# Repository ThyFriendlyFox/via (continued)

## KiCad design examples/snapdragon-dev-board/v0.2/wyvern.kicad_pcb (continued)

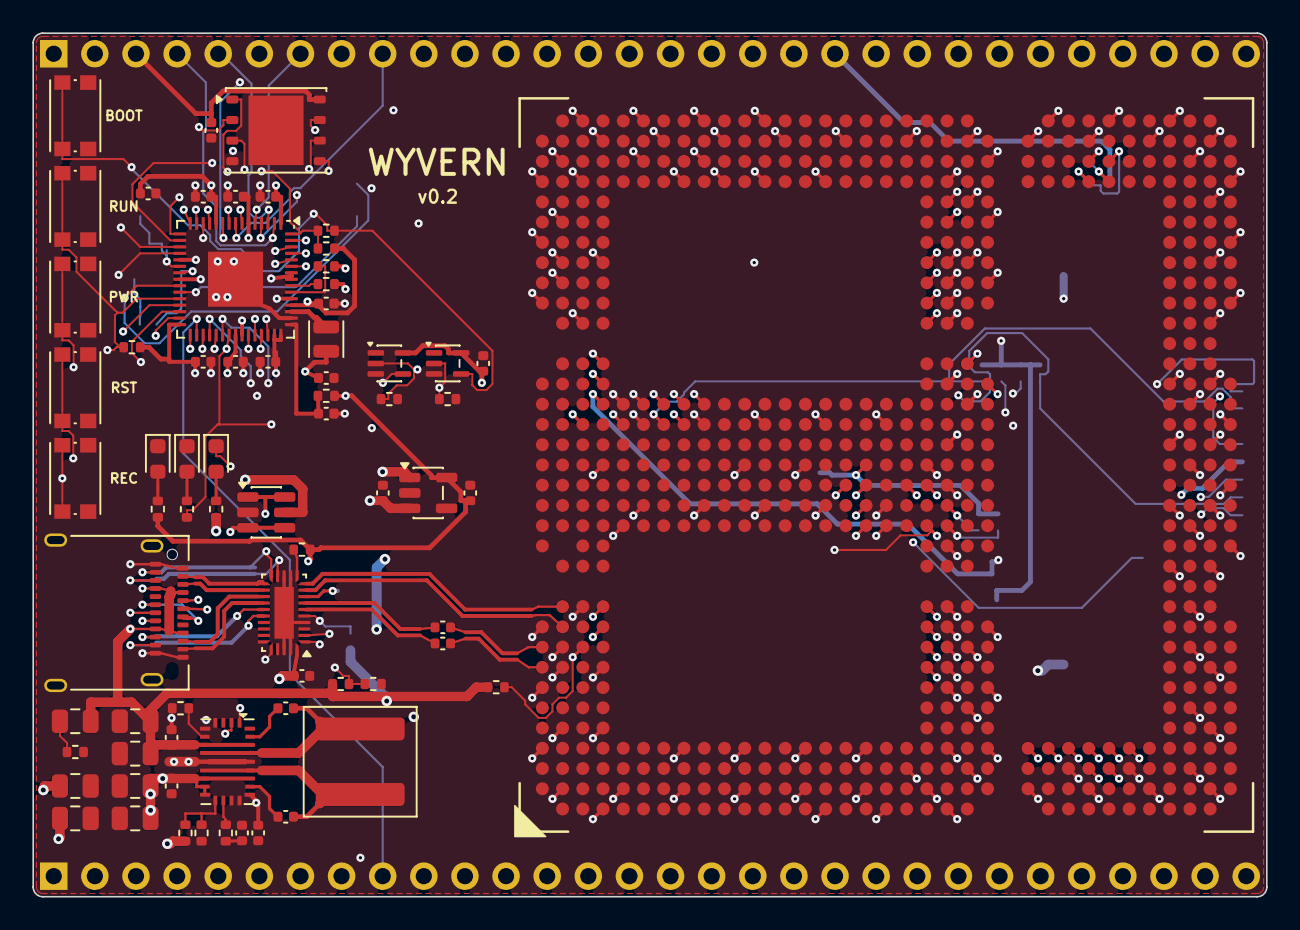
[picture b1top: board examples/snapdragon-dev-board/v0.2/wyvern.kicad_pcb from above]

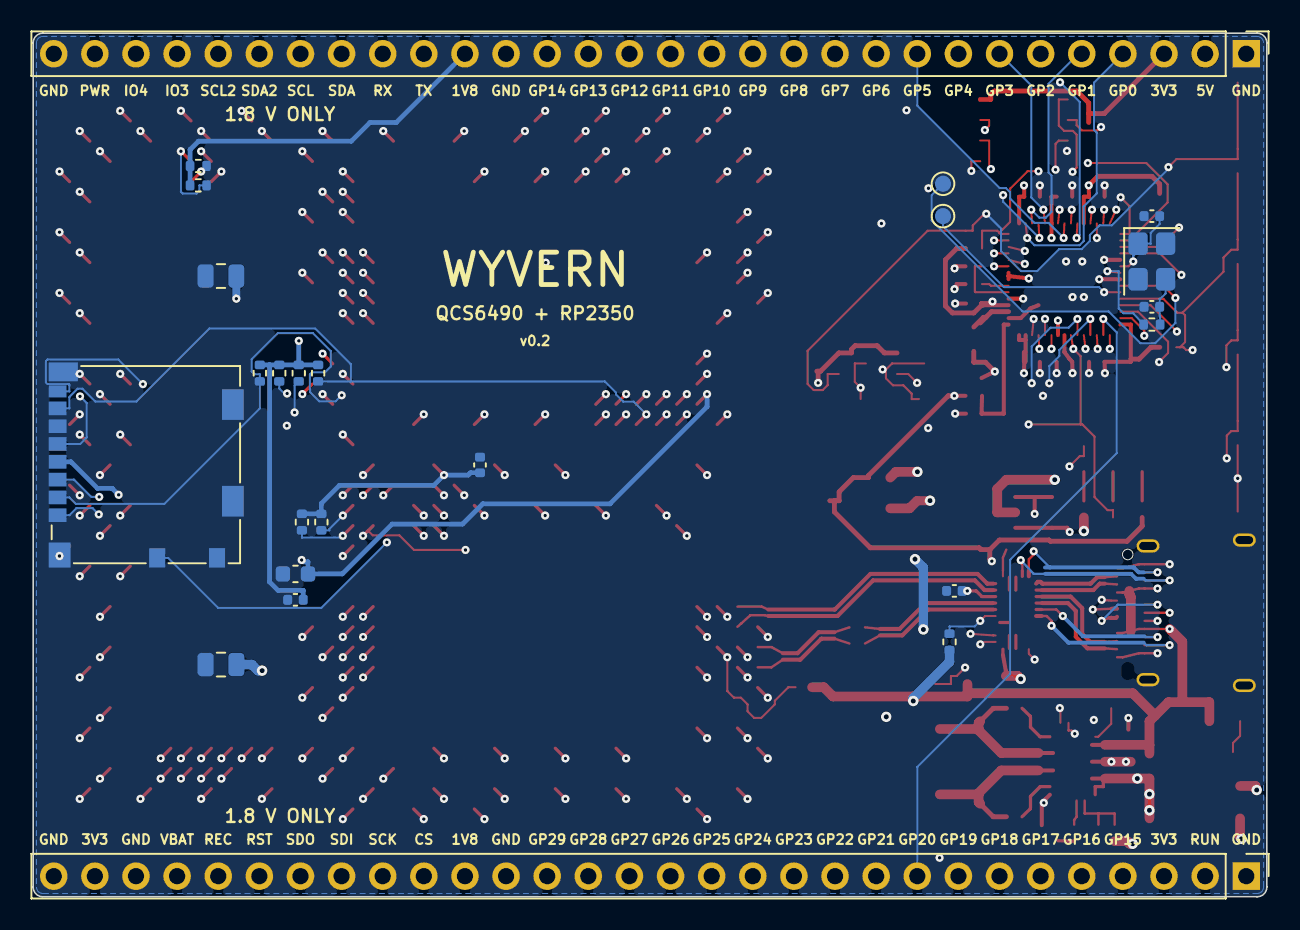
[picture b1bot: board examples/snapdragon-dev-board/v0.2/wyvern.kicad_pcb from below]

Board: 6 copper layers, 76.2 x 53.3 mm, 94 parts (24 on the bottom side), 118 nets.

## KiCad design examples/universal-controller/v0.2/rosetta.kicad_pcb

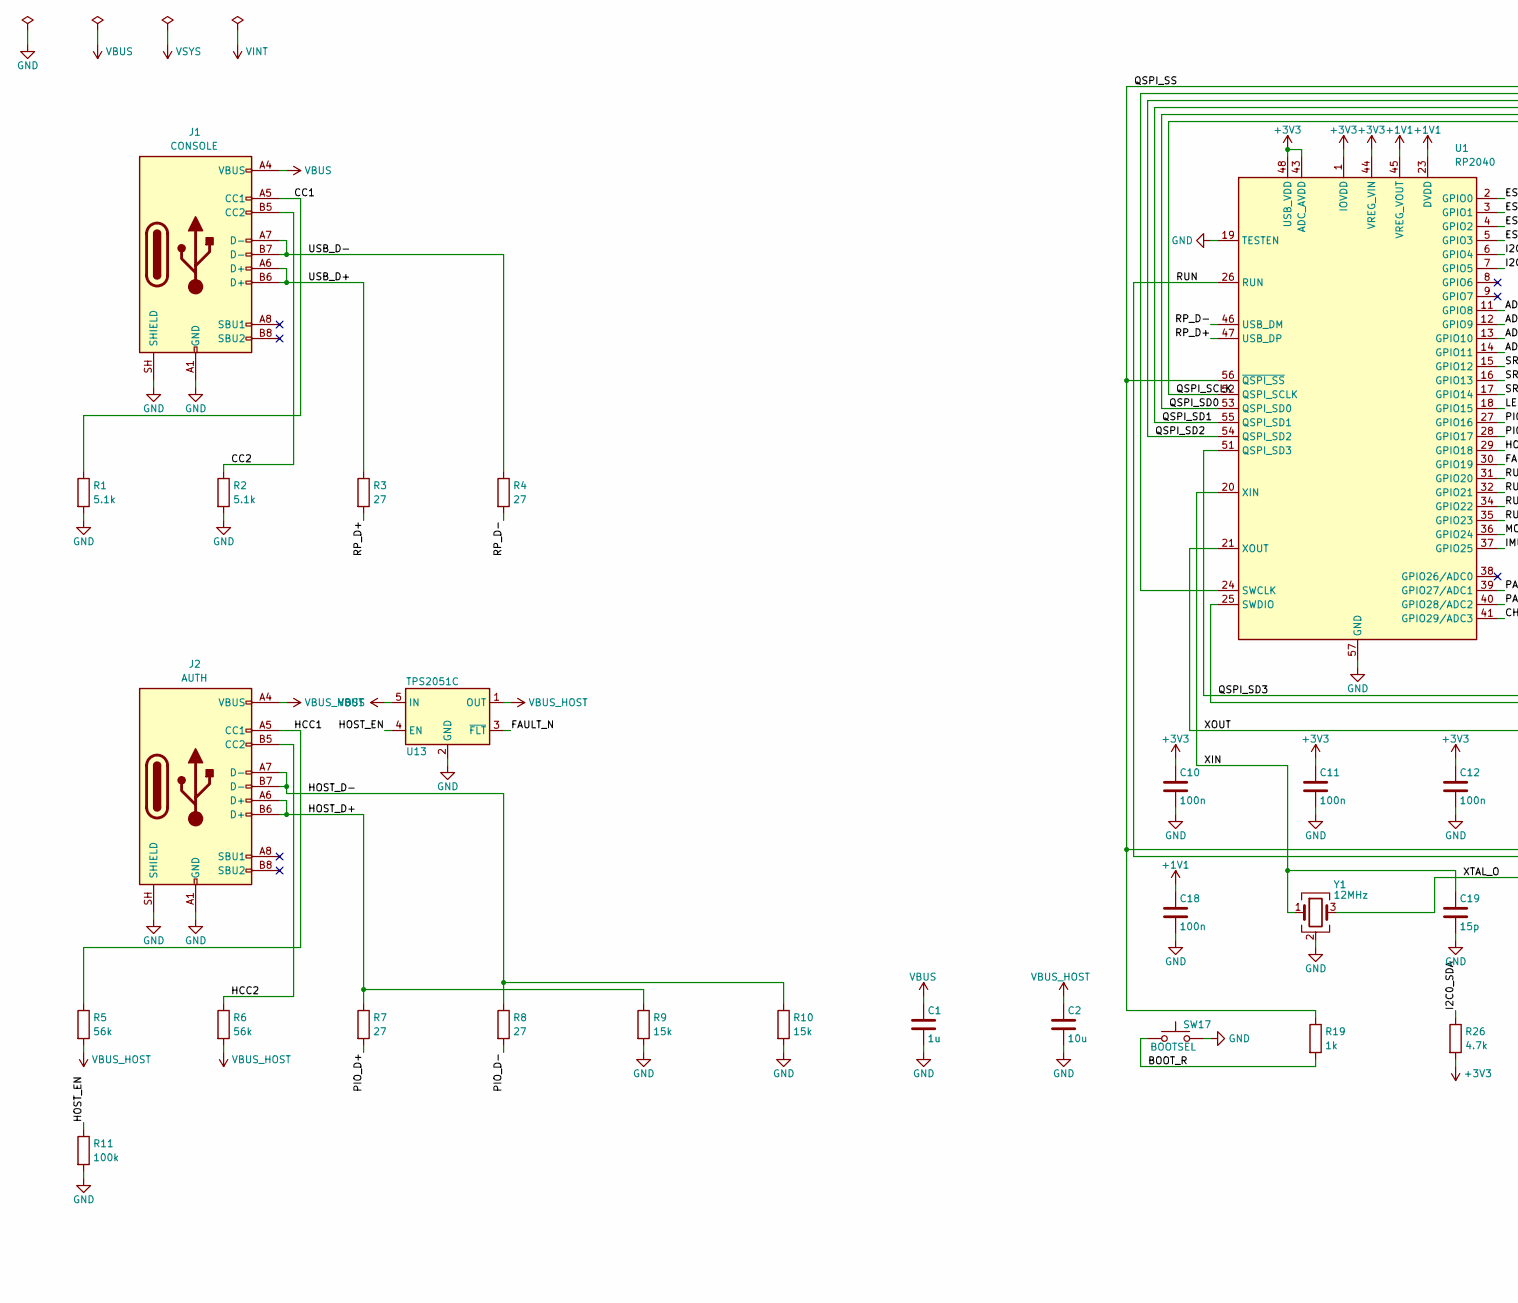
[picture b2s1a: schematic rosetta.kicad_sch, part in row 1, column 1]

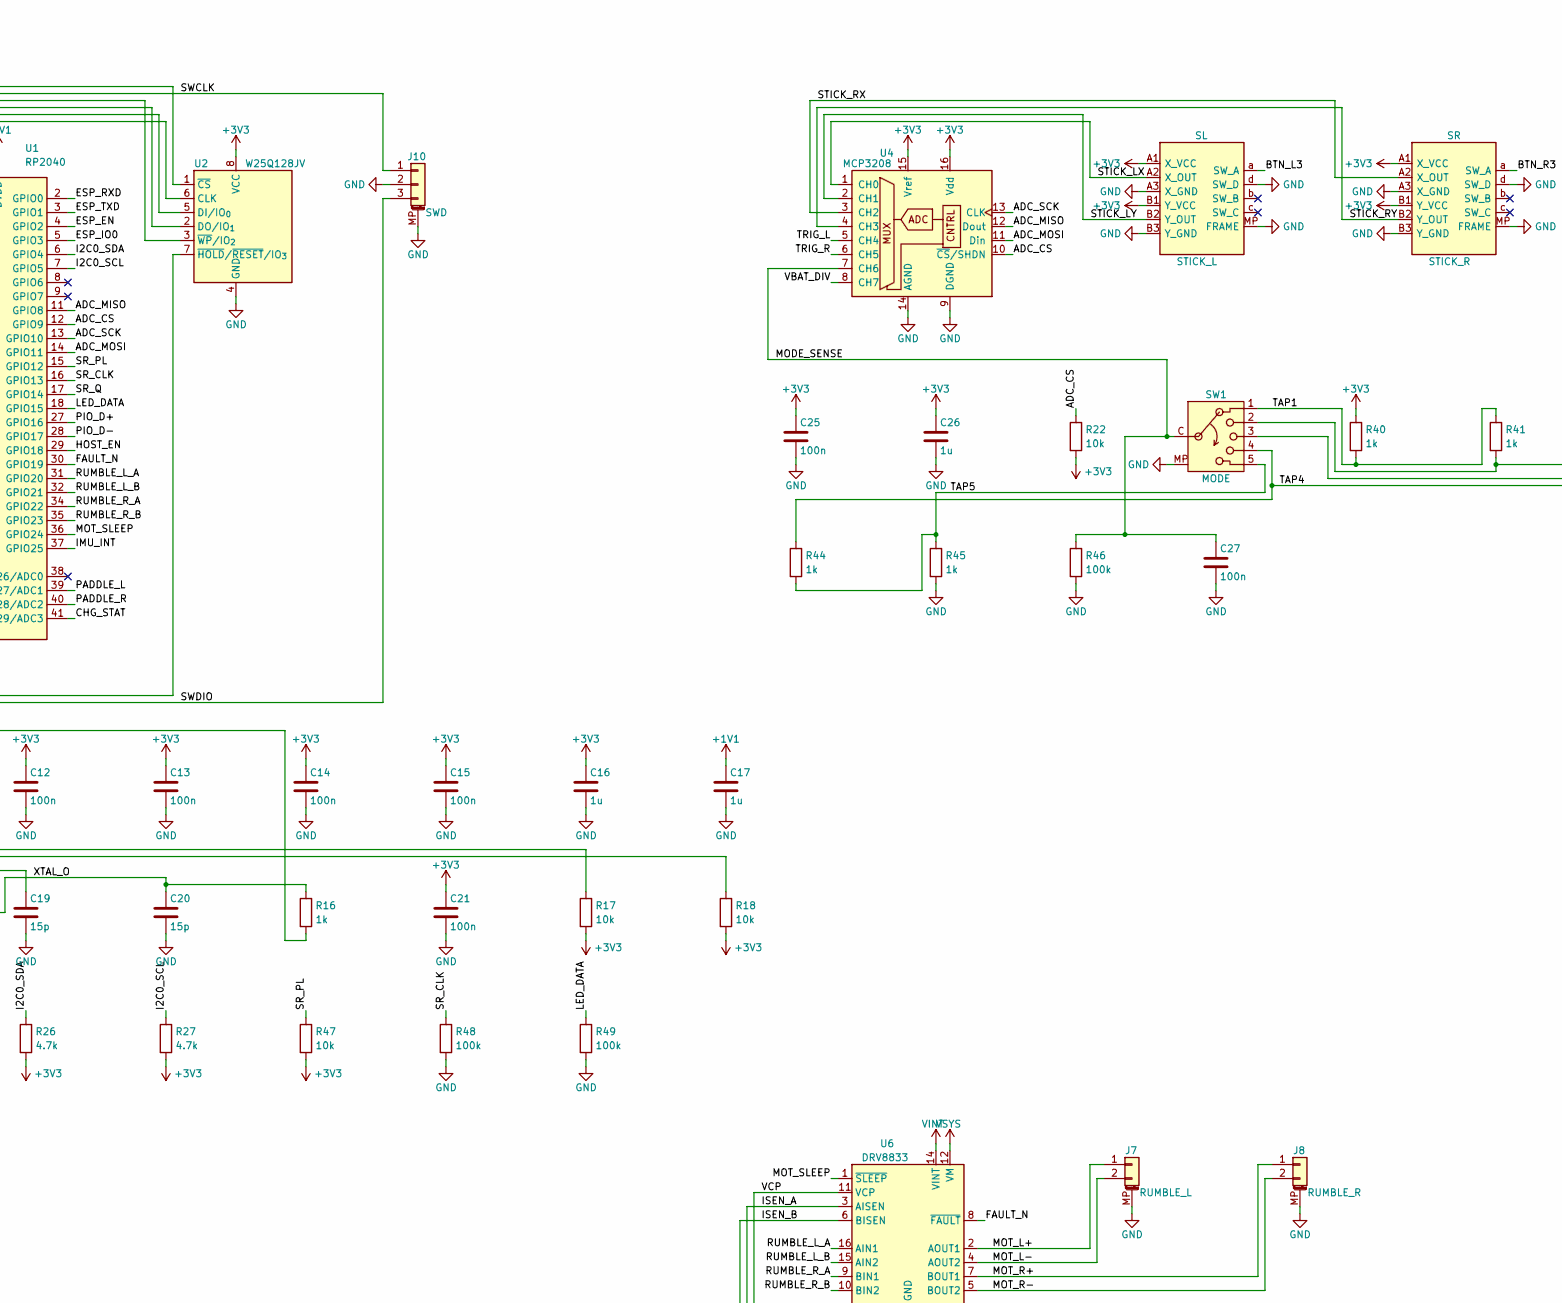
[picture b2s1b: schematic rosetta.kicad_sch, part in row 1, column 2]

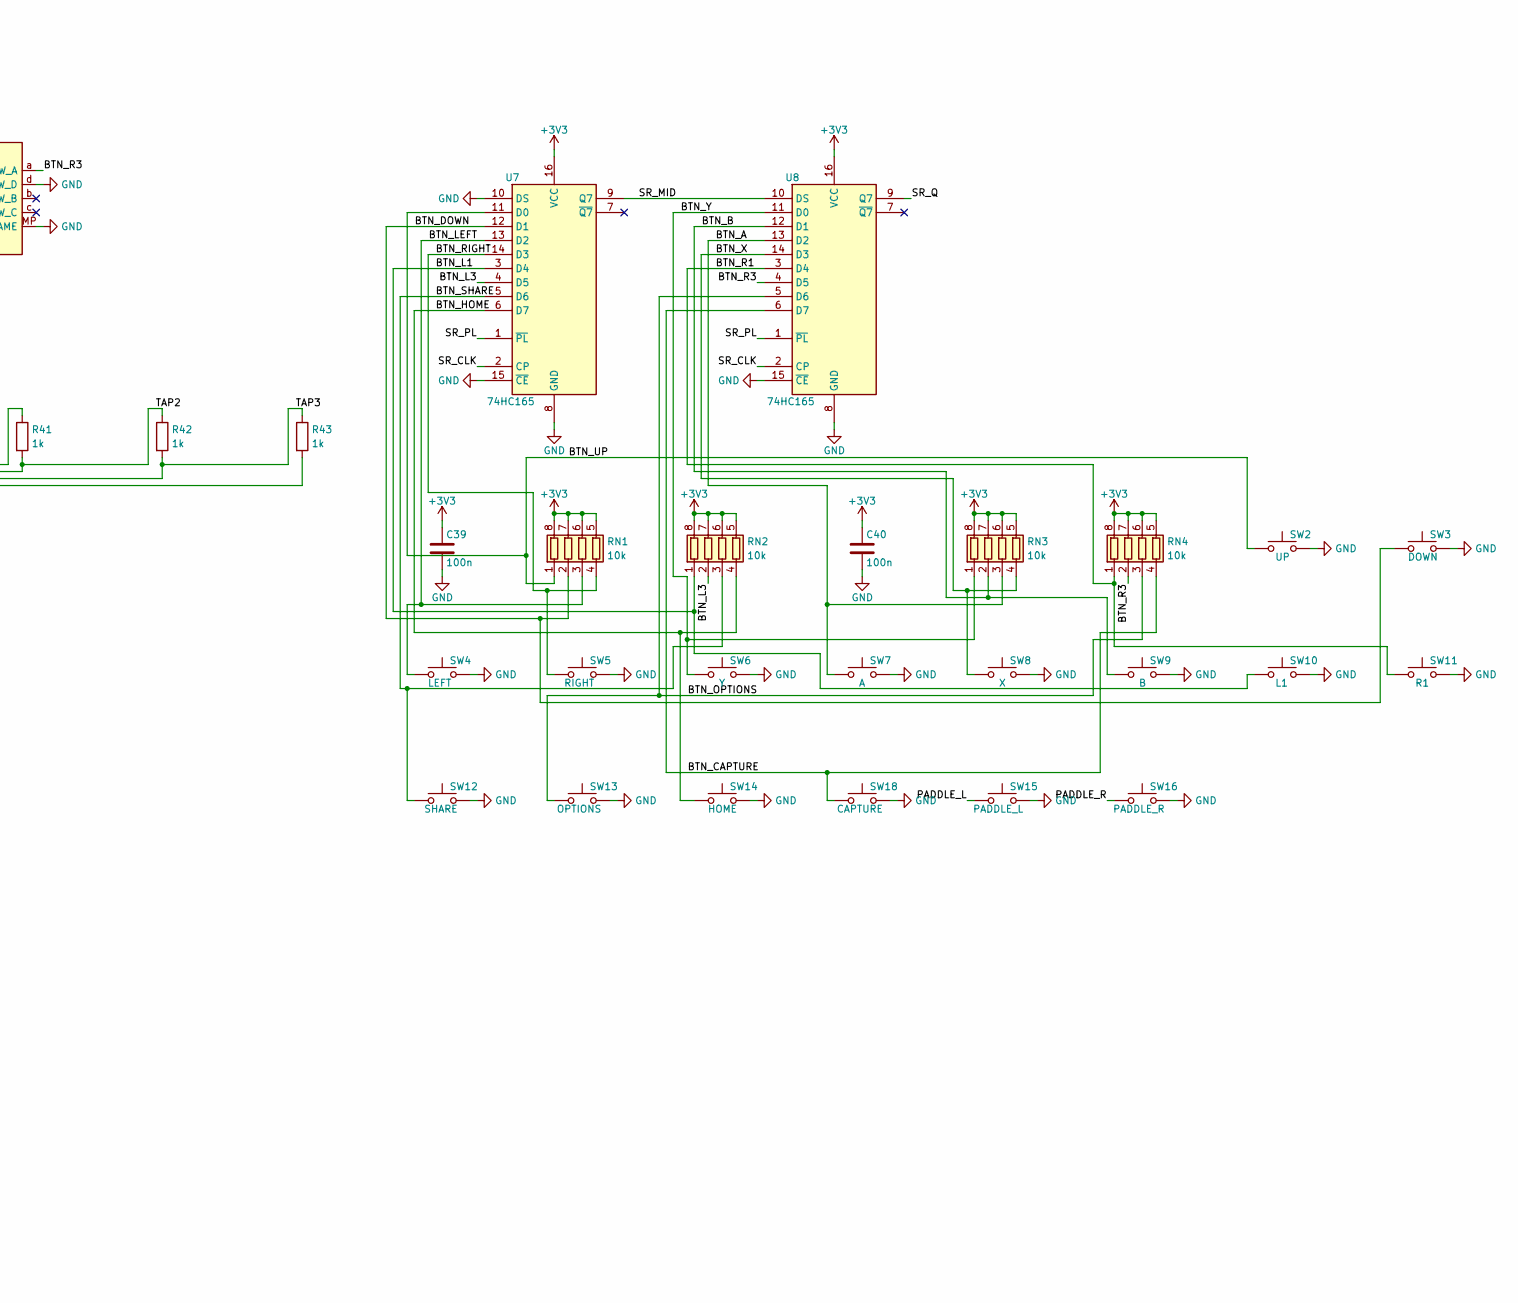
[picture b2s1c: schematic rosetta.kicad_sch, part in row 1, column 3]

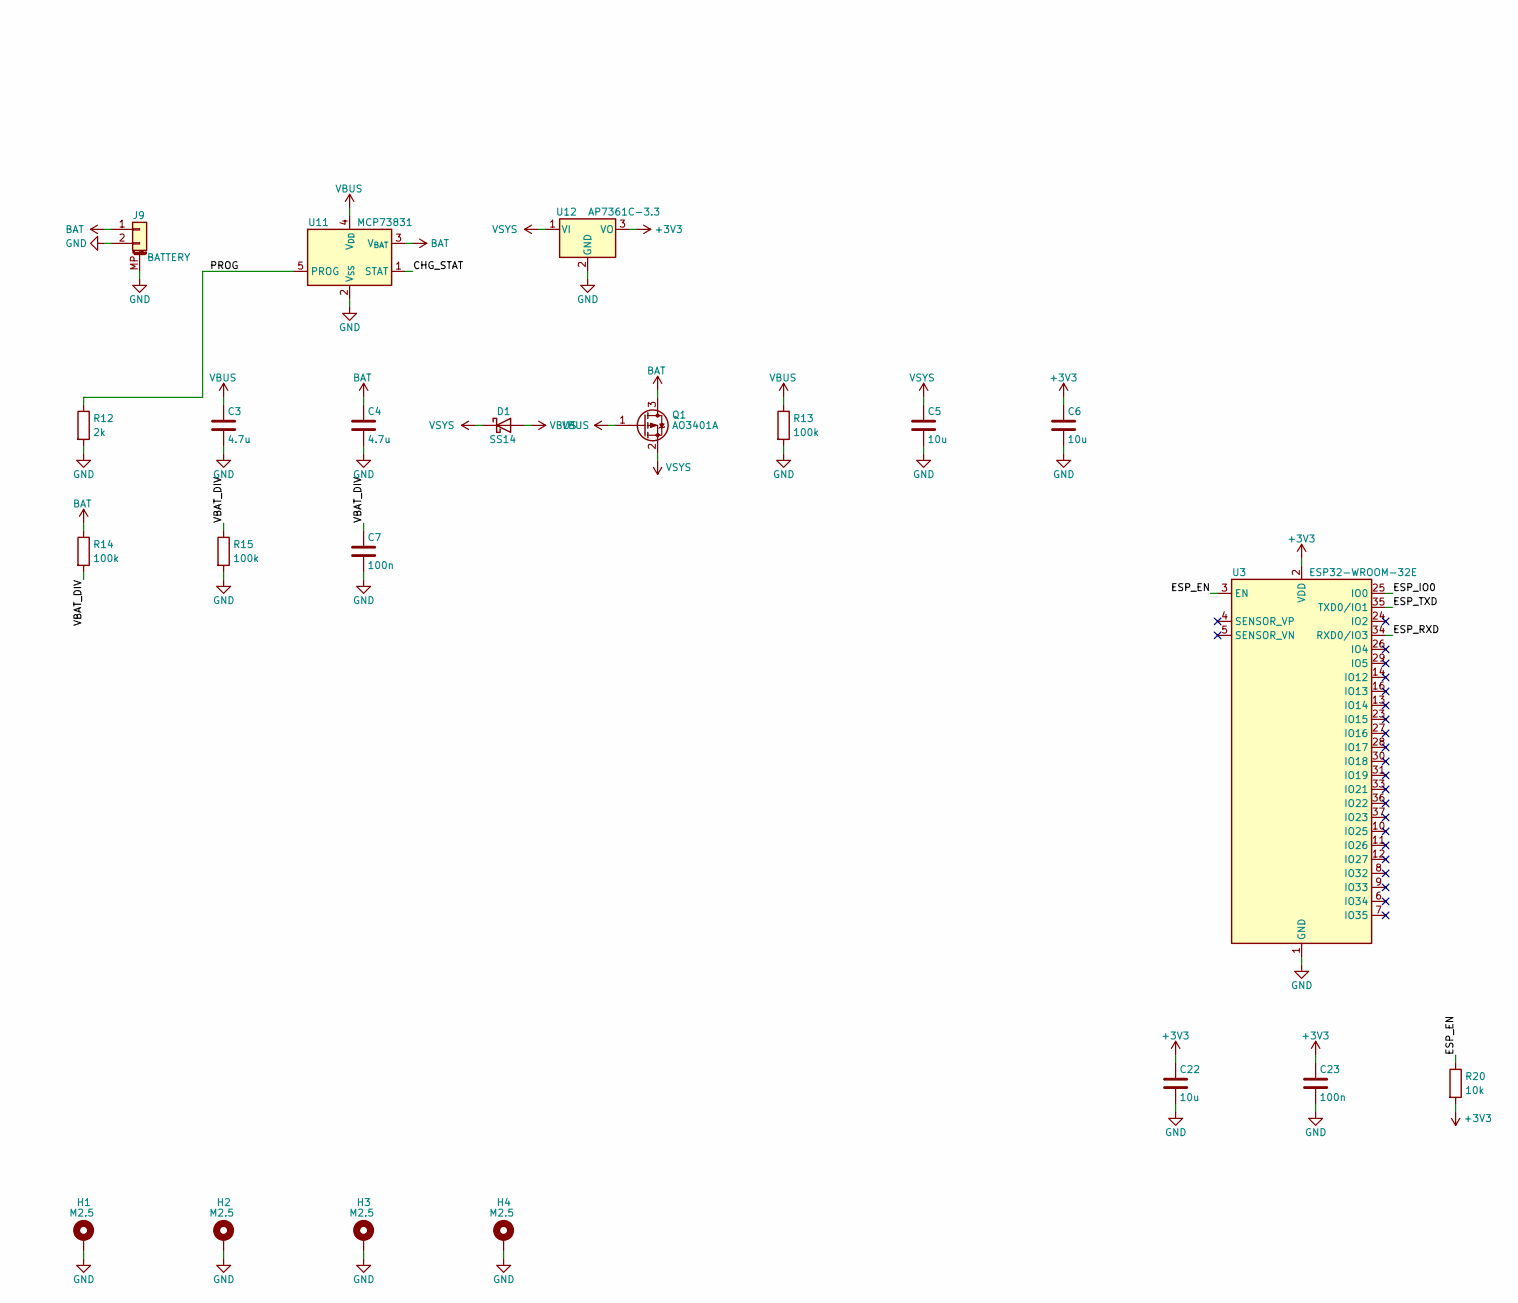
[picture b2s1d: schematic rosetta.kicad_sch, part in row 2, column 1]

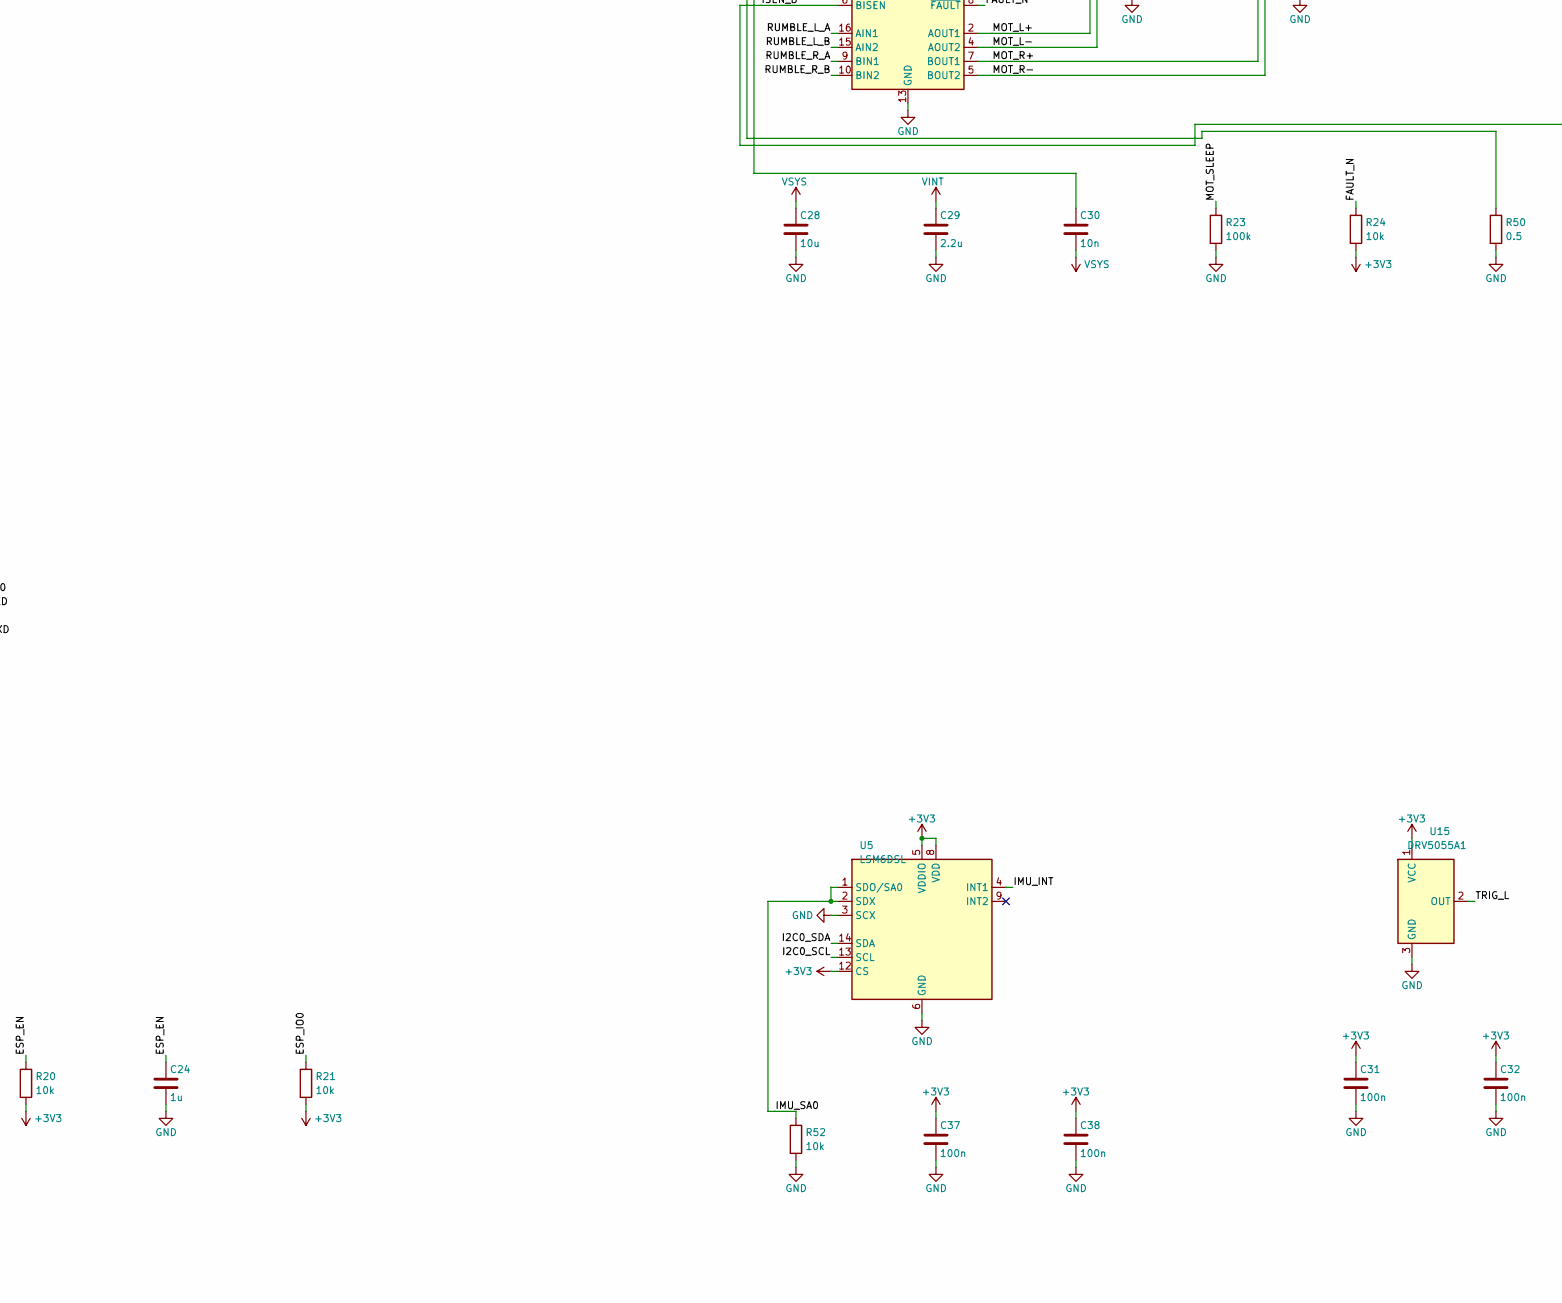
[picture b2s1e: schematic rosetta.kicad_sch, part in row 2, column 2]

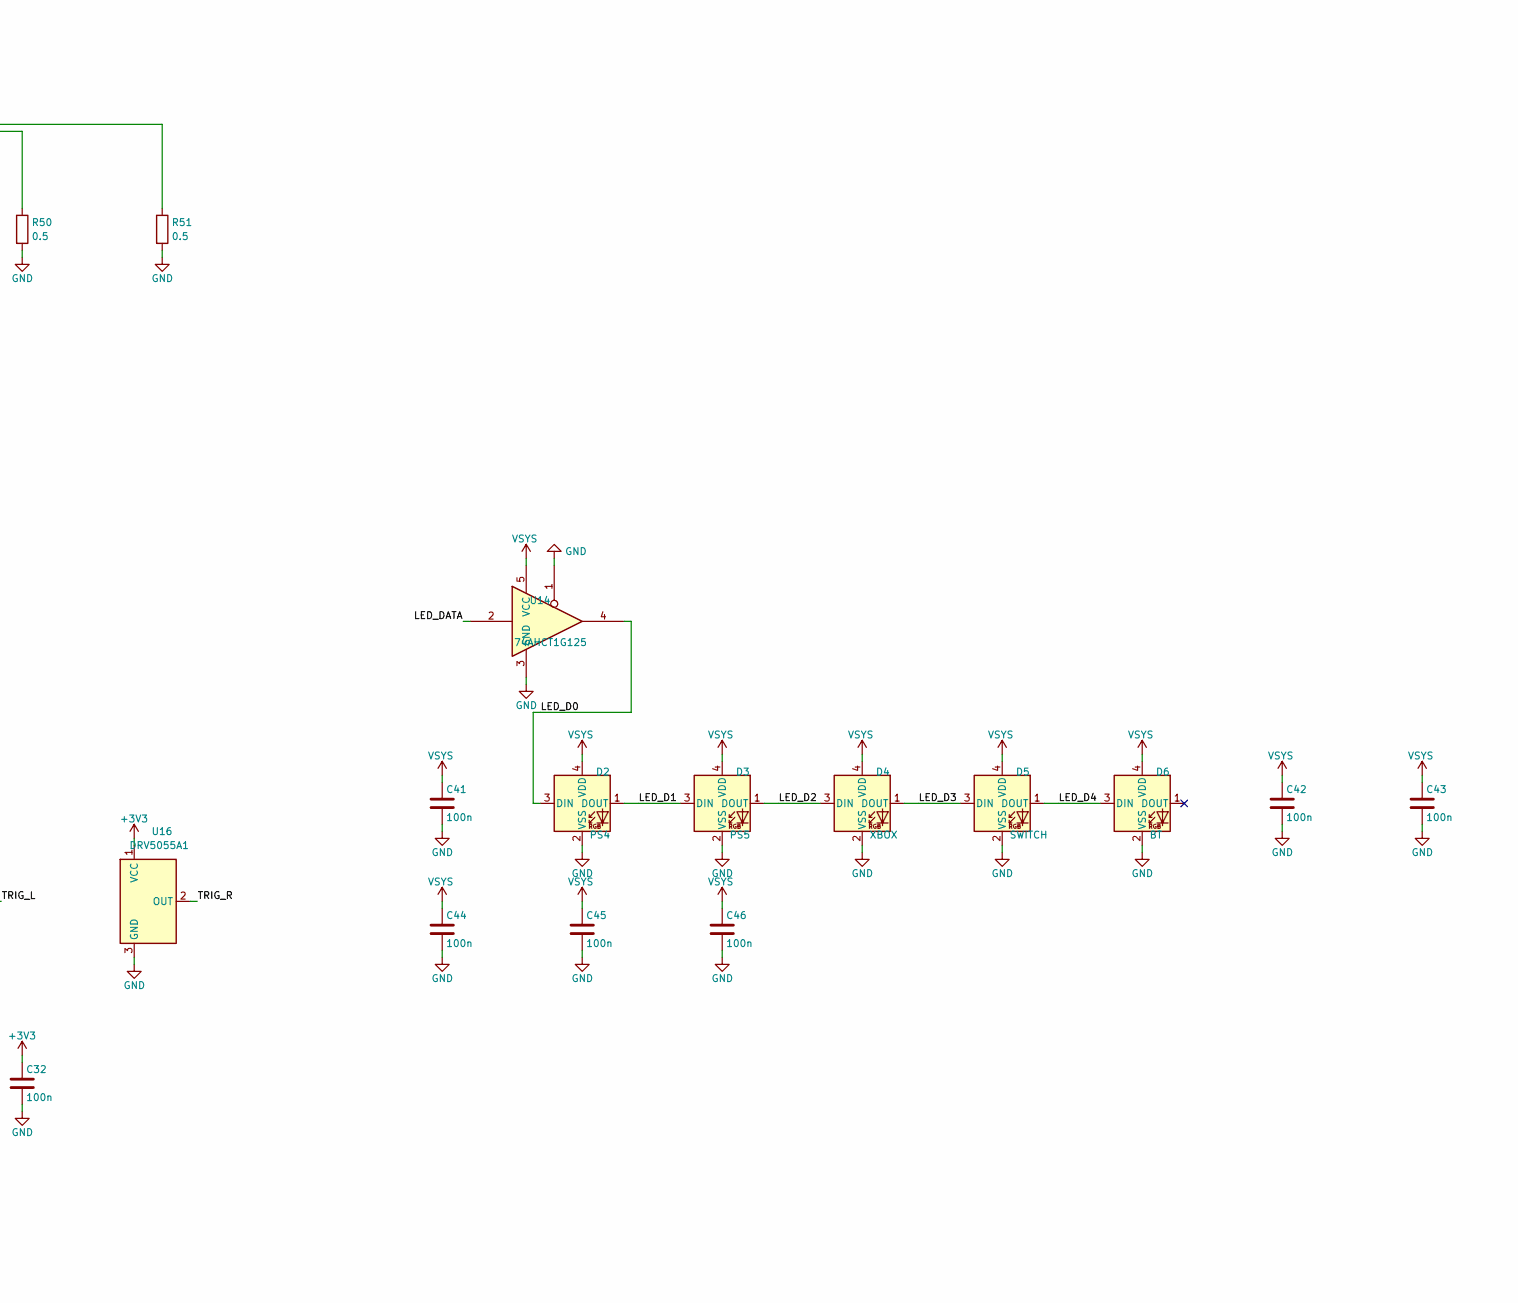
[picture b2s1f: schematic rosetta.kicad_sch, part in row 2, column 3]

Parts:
C1, C16, C17, C24, C26: 1u; C_0603_1608Metric
C2, C5, C6, C22, C28: 10u; C_0805_2012Metric
C3, C4: 4.7u; C_0805_2012Metric
C7, C10, C11, C12, C13, C14, C15, C18, C21, C23, C25, C27, C31, C32, C37, C38, C39, C40, C41, C42, C43, C44, C45, C46: 100n; C_0603_1608Metric
C19, C20: 15p; C_0603_1608Metric
C29: 2.2u; C_0603_1608Metric
C30: 10n; C_0603_1608Metric
D1: SS14; D_SOD-123
D2: PS4; LED_WS2812B-2020_PLCC4_2.0x2.0mm
D3: PS5; LED_WS2812B-2020_PLCC4_2.0x2.0mm
D4: XBOX; LED_WS2812B-2020_PLCC4_2.0x2.0mm
D5: SWITCH; LED_WS2812B-2020_PLCC4_2.0x2.0mm
D6: BT; LED_WS2812B-2020_PLCC4_2.0x2.0mm
H1, H2, H3, H4: M2.5; MountingHole_2.5mm_Pad
J1: CONSOLE; USB_C_Receptacle_GCT_USB4085
J2: AUTH; USB_C_Receptacle_GCT_USB4085
J7: RUMBLE_L; JST_SH_SM02B-SRSS-TB_1x02-1MP_P1.00mm_Horizontal
J8: RUMBLE_R; JST_SH_SM02B-SRSS-TB_1x02-1MP_P1.00mm_Horizontal
J9: BATTERY; JST_PH_S2B-PH-SM4-TB_1x02-1MP_P2.00mm_Horizontal
J10: SWD; JST_SH_SM03B-SRSS-TB_1x03-1MP_P1.00mm_Horizontal
Q1: AO3401A; SOT-23
R1, R2: 5.1k; R_0603_1608Metric
R3, R4, R7, R8: 27; R_0603_1608Metric
R5, R6: 56k; R_0603_1608Metric
R9, R10: 15k; R_0603_1608Metric
R11, R13, R14, R15, R23, R46, R48, R49: 100k; R_0603_1608Metric
R12: 2k; R_0603_1608Metric
R16, R19, R40, R41, R42, R43, R44, R45: 1k; R_0603_1608Metric
R17, R18, R20, R21, R22, R24, R47, R52: 10k; R_0603_1608Metric
R26, R27: 4.7k; R_0603_1608Metric
R50, R51: 0.5; R_0603_1608Metric
RN1, RN2, RN3, RN4: 10k; R_Array_Convex_4x0603
SL: STICK_L; Thumbstick_ALPS_RKJXV122400R
SR: STICK_R; Thumbstick_ALPS_RKJXV122400R
SW1: MODE; SW_NKK_NR01
SW2: UP; SW_SPST_TL3342
SW3: DOWN; SW_SPST_TL3342
SW4: LEFT; SW_SPST_TL3342
SW5: RIGHT; SW_SPST_TL3342
SW6: Y; SW_SPST_TL3342
SW7: A; SW_SPST_TL3342
SW8: X; SW_SPST_TL3342
SW9: B; SW_SPST_TL3342
SW10: L1; SW_Tactile_SPST_Angled_PTS645Vx31-2LFS
SW11: R1; SW_Tactile_SPST_Angled_PTS645Vx31-2LFS
SW12: SHARE; SW_SPST_PTS810
SW13: OPTIONS; SW_SPST_PTS810
SW14: HOME; SW_SPST_PTS810
SW15: PADDLE_L; SW_SPST_TL3342
SW16: PADDLE_R; SW_SPST_TL3342
SW17: BOOTSEL; SW_SPST_PTS810
SW18: CAPTURE; SW_SPST_PTS810
U1: RP2040; QFN-56-1EP_7x7mm_P0.4mm_EP3.2x3.2mm
U2: W25Q128JV; SOIC-8_5.3x5.3mm_P1.27mm
U3: ESP32-WROOM-32E
U4: MCP3208; SOIC-16_3.9x9.9mm_P1.27mm
U5: LSM6DSL; LGA-14_3x2.5mm_P0.5mm_LayoutBorder3x4y
U6: DRV8833; TSSOP-16_4.4x5mm_P0.65mm
U7, U8: 74HC165; SOIC-16_3.9x9.9mm_P1.27mm
U11: MCP73831; SOT-23-5
U12: AP7361C-3.3; SOT-223-3_TabPin2
U13: TPS2051C; SOT-23-5
U14: 74AHCT1G125; SOT-23-5
U15, U16: DRV5055A1; SOT-23
Y1: 12MHz; Crystal_SMD_3225-4Pin_3.2x2.5mm

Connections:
+1V1: C17.1, C18.1, U1.23 (DVDD), U1.45 (VREG_VOUT), U1.50 (DVDD)
+3V3: C6.1, C10.1, C11.1, C12.1, C13.1, C14.1, C15.1, C16.1, C21.1, C22.1, C23.1, C25.1, C26.1, C31.1, C32.1, C37.1, C38.1, C39.1, C40.1, R17.2, R18.2, R20.2, R21.2, R22.2, R24.2, R26.2, R27.2, R40.1, R47.2, RN1.5 (R4.2), RN1.6 (R3.2), RN1.7 (R2.2), RN1.8 (R1.2), RN2.5 (R4.2), RN2.6 (R3.2), RN2.7 (R2.2), RN2.8 (R1.2), RN3.5 (R4.2), RN3.6 (R3.2), RN3.7 (R2.2), RN3.8 (R1.2), RN4.5 (R4.2), RN4.6 (R3.2), RN4.7 (R2.2), RN4.8 (R1.2), SL.A1 (X_VCC), SL.B1 (Y_VCC), SR.A1 (X_VCC), SR.B1 (Y_VCC), U1.1 (IOVDD), U1.10 (IOVDD), U1.22 (IOVDD), U1.33 (IOVDD), U1.42 (IOVDD), U1.43 (ADC_AVDD), U1.44 (VREG_VIN), U1.48 (USB_VDD), U1.49 (IOVDD), U2.8 (VCC), U3.2 (VDD), U4.15 (Vref), U4.16 (Vdd), U5.5 (VDDIO), U5.8 (VDD), U5.12 (CS), U7.16 (VCC), U8.16 (VCC), U12.3 (VO), U15.1 (VCC), U16.1 (VCC)
/ADC_CS: R22.1, U1.12 (GPIO9), U4.10 (~CS/SHDN)
/ADC_MISO: U1.11 (GPIO8), U4.12 (Dout)
/ADC_MOSI: U1.14 (GPIO11), U4.11 (Din)
/ADC_SCK: U1.13 (GPIO10), U4.13 (CLK)
/BOOT_R: R19.2, SW17.1
/BTN_A: RN3.3 (R3.1), SW7.1, U8.13 (D2)
/BTN_B: RN3.2 (R2.1), SW9.1, U8.12 (D1)
/BTN_CAPTURE: RN4.4 (R4.1), SW18.1, U8.6 (D7)
/BTN_DOWN: RN1.2 (R2.1), SW3.1, U7.12 (D1)
/BTN_HOME: RN2.4 (R4.1), SW14.1, U7.6 (D7)
/BTN_L1: RN2.1 (R1.1), SW10.1, U7.3 (D4)
/BTN_L3: RN2.2 (R2.1), SL.a (SW_A), U7.4 (D5)
/BTN_LEFT: RN1.3 (R3.1), SW4.1, U7.13 (D2)
/BTN_OPTIONS: RN4.3 (R3.1), SW13.1, U8.5 (D6)
/BTN_R1: RN4.1 (R1.1), SW11.1, U8.3 (D4)
/BTN_R3: RN4.2 (R2.1), SR.a (SW_A), U8.4 (D5)
/BTN_RIGHT: RN1.4 (R4.1), SW5.1, U7.14 (D3)
/BTN_SHARE: RN2.3 (R3.1), SW12.1, U7.5 (D6)
/BTN_UP: RN1.1 (R1.1), SW2.1, U7.11 (D0)
/BTN_X: RN3.4 (R4.1), SW8.1, U8.14 (D3)
/BTN_Y: RN3.1 (R1.1), SW6.1, U8.11 (D0)
/CC1: J1.A5 (CC1), R1.1
/CC2: J1.B5 (CC2), R2.1
/CHG_STAT: U1.41 (GPIO29/ADC3), U11.1 (STAT)
/ESP_EN: C24.1, R20.1, U1.4 (GPIO2), U3.3 (EN)
/ESP_IO0: R21.1, U1.5 (GPIO3), U3.25 (IO0)
/ESP_RXD: U1.2 (GPIO0), U3.34 (RXD0/IO3)
/ESP_TXD: U1.3 (GPIO1), U3.35 (TXD0/IO1)
/FAULT_N: R24.1, U1.30 (GPIO19), U6.8 (~FAULT), U13.3 (~FLT)
/HCC1: J2.A5 (CC1), R5.1
/HCC2: J2.B5 (CC2), R6.1
/HOST_D+: J2.A6 (D+), J2.B6 (D+), R7.1, R9.1
/HOST_D-: J2.A7 (D-), J2.B7 (D-), R8.1, R10.1
/HOST_EN: R11.1, U1.29 (GPIO18), U13.4 (EN)
/I2C0_SCL: R27.1, U1.7 (GPIO5), U5.13 (SCL)
/I2C0_SDA: R26.1, U1.6 (GPIO4), U5.14 (SDA)
/IMU_INT: U1.37 (GPIO25), U5.4 (INT1)
/IMU_SA0: R52.1, U5.1 (SDO/SA0), U5.2 (SDX)
/ISEN_A: R50.1, U6.3 (AISEN)
/ISEN_B: R51.1, U6.6 (BISEN)
/LED_D0: D2.3 (DIN), U14.4
/LED_D1: D2.1 (DOUT), D3.3 (DIN)
/LED_D2: D3.1 (DOUT), D4.3 (DIN)
/LED_D3: D4.1 (DOUT), D5.3 (DIN)
/LED_D4: D5.1 (DOUT), D6.3 (DIN)
/LED_DATA: R49.1, U1.18 (GPIO15), U14.2
/MODE_SENSE: C27.1, R46.1, SW1.C (Common), U4.7 (CH6)
/MOT_L+: J7.1, U6.2 (AOUT1)
/MOT_L-: J7.2, U6.4 (AOUT2)
/MOT_R+: J8.1, U6.7 (BOUT1)
/MOT_R-: J8.2, U6.5 (BOUT2)
/MOT_SLEEP: R23.1, U1.36 (GPIO24), U6.1 (~SLEEP)
/PADDLE_L: SW15.1, U1.39 (GPIO27/ADC1)
/PADDLE_R: SW16.1, U1.40 (GPIO28/ADC2)
/PIO_D+: R7.2, U1.27 (GPIO16)
/PIO_D-: R8.2, U1.28 (GPIO17)
/PROG: R12.1, U11.5 (PROG)
/QSPI_SCLK: U1.52 (QSPI_SCLK), U2.6 (CLK)
/QSPI_SD0: U1.53 (QSPI_SD0), U2.5 (DI/IO_{0})
/QSPI_SD1: U1.55 (QSPI_SD1), U2.2 (DO/IO_{1})
/QSPI_SD2: U1.54 (QSPI_SD2), U2.3 (~WP/IO_{2})
/QSPI_SD3: U1.51 (QSPI_SD3), U2.7 (~HOLD/~RESET/IO_{3})
/QSPI_SS: R17.1, R19.1, U1.56 (~QSPI_SS), U2.1 (~CS)
/RP_D+: R3.2, U1.47 (USB_DP)
/RP_D-: R4.2, U1.46 (USB_DM)
/RUMBLE_L_A: U1.31 (GPIO20), U6.16 (AIN1)
/RUMBLE_L_B: U1.32 (GPIO21), U6.15 (AIN2)
/RUMBLE_R_A: U1.34 (GPIO22), U6.9 (BIN1)
/RUMBLE_R_B: U1.35 (GPIO23), U6.10 (BIN2)
/RUN: R18.1, U1.26 (RUN)
/SR_CLK: R48.1, U1.16 (GPIO13), U7.2 (CP), U8.2 (CP)
/SR_MID: U7.9 (Q7), U8.10 (DS)
/SR_PL: R47.1, U1.15 (GPIO12), U7.1 (~PL), U8.1 (~PL)
/SR_Q: U1.17 (GPIO14), U8.9 (Q7)
/STICK_LX: SL.A2 (X_OUT), U4.1 (CH0)
/STICK_LY: SL.B2 (Y_OUT), U4.2 (CH1)
/STICK_RX: SR.A2 (X_OUT), U4.3 (CH2)
/STICK_RY: SR.B2 (Y_OUT), U4.4 (CH3)
/SWCLK: J10.1, U1.24 (SWCLK)
/SWDIO: J10.3, U1.25 (SWDIO)
/TAP1: R40.2, R41.1, SW1.1
/TAP2: R41.2, R42.1, SW1.2
/TAP3: R42.2, R43.1, SW1.3
/TAP4: R43.2, R44.1, SW1.4
/TAP5: R44.2, R45.1, SW1.5
/TRIG_L: U4.5 (CH4), U15.2 (OUT)
/TRIG_R: U4.6 (CH5), U16.2 (OUT)
/USB_D+: J1.A6 (D+), J1.B6 (D+), R3.1
/USB_D-: J1.A7 (D-), J1.B7 (D-), R4.1
/VBAT_DIV: C7.1, R14.2, R15.1, U4.8 (CH7)
/VCP: C30.1, U6.11 (VCP)
/XIN: C19.1, U1.20 (XIN), Y1.1
/XOUT: R16.2, U1.21 (XOUT)
/XTAL_O: C20.1, R16.1, Y1.3
BAT: C4.1, J9.1, Q1.3 (D), R14.1, U11.3 (V_{BAT})
GND: C1.2, C2.2, C3.2, C4.2, C5.2, C6.2, C7.2, C10.2, C11.2, C12.2, C13.2, C14.2, C15.2, C16.2, C17.2, C18.2, C19.2, C20.2, C21.2, C22.2, C23.2, C24.2, C25.2, C26.2, C27.2, C28.2, C29.2, C31.2, C32.2, C37.2, C38.2, C39.2, C40.2, C41.2, C42.2, C43.2, C44.2, C45.2, C46.2, D2.2 (VSS), D3.2 (VSS), D4.2 (VSS), D5.2 (VSS), D6.2 (VSS), H1.1, H2.1, H3.1, H4.1, J1.A1 (GND), J1.A12 (GND), J1.B1 (GND), J1.B12 (GND), J1.SH (SHIELD), J2.A1 (GND), J2.A12 (GND), J2.B1 (GND), J2.B12 (GND), J2.SH (SHIELD), J7.MP (MountPin), J8.MP (MountPin), J9.2, J9.MP (MountPin), J10.2, J10.MP (MountPin), R1.2, R2.2, R9.2, R10.2, R11.2, R12.2, R13.2, R15.2, R23.2, R45.2, R46.2, R48.2, R49.2, R50.2, R51.2, R52.2, SL.A3 (X_GND), SL.B3 (Y_GND), SL.MP (FRAME), SL.d (SW_D), SR.A3 (X_GND), SR.B3 (Y_GND), SR.MP (FRAME), SR.d (SW_D), SW1.MP, SW2.2, SW3.2, SW4.2, SW5.2, SW6.2, SW7.2, SW8.2, SW9.2, SW10.2, SW11.2, SW12.2, SW13.2, SW14.2, SW15.2, SW16.2, SW17.2, SW18.2, U1.19 (TESTEN), U1.57 (GND), U2.4 (GND), U3.1 (GND), U3.15 (GND), U3.38 (GND), U3.39 (GND), U4.9 (DGND), U4.14 (AGND), U5.3 (SCX), U5.6 (GND), U5.7 (GND), U6.13 (GND), U7.8 (GND), U7.10 (DS), U7.15 (~CE), U8.8 (GND), U8.15 (~CE), U11.2 (V_{SS}), U12.2 (GND), U13.2 (GND), U14.1, U14.3 (GND), U15.3 (GND), U16.3 (GND), Y1.2 (G), Y1.4 (G)
VBUS: C1.1, C3.1, D1.2 (A), J1.A4 (VBUS), J1.A9 (VBUS), J1.B4 (VBUS), J1.B9 (VBUS), Q1.1 (G), R13.1, U11.4 (V_{DD}), U13.5 (IN)
VBUS_HOST: C2.1, J2.A4 (VBUS), J2.A9 (VBUS), J2.B4 (VBUS), J2.B9 (VBUS), R5.2, R6.2, U13.1 (OUT)
VINT: C29.1, U6.14 (VINT)
VSYS: C5.1, C28.1, C30.2, C41.1, C42.1, C43.1, C44.1, C45.1, C46.1, D1.1 (K), D2.4 (VDD), D3.4 (VDD), D4.4 (VDD), D5.4 (VDD), D6.4 (VDD), Q1.2 (S), U6.12 (VM), U12.1 (VI), U14.5 (VCC)

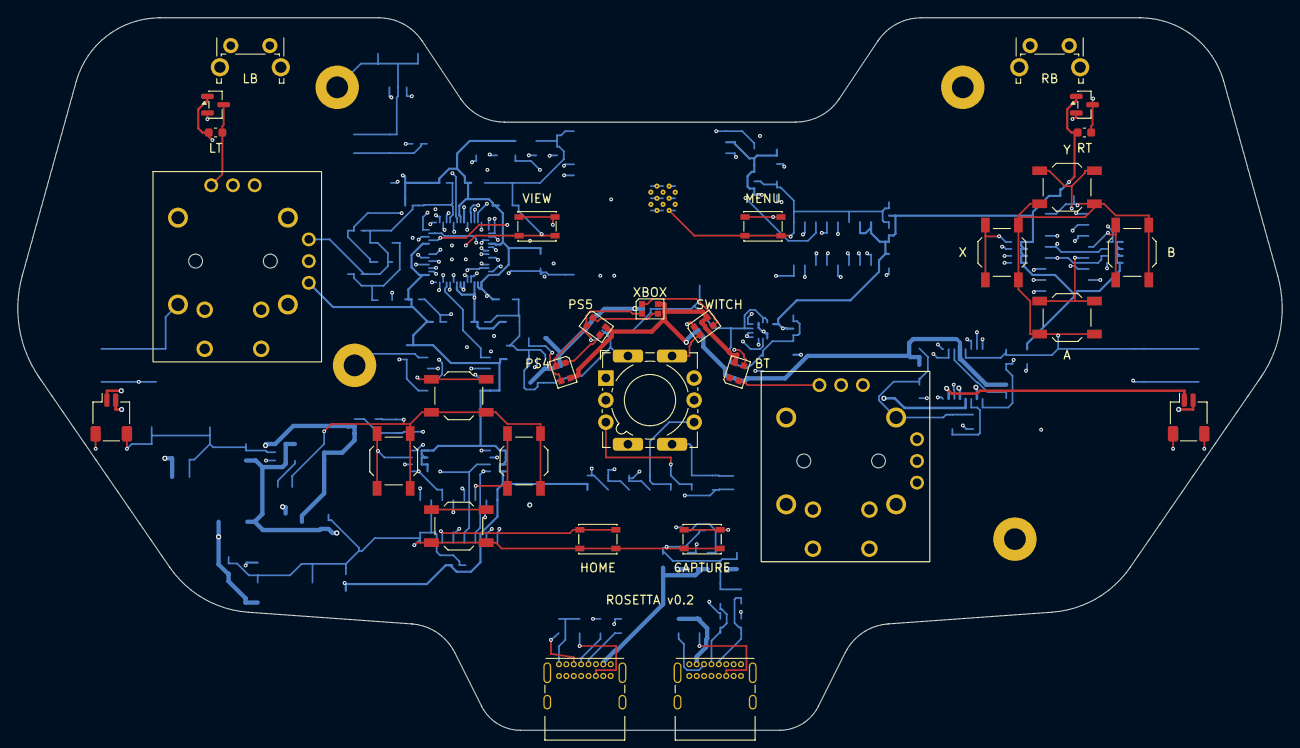
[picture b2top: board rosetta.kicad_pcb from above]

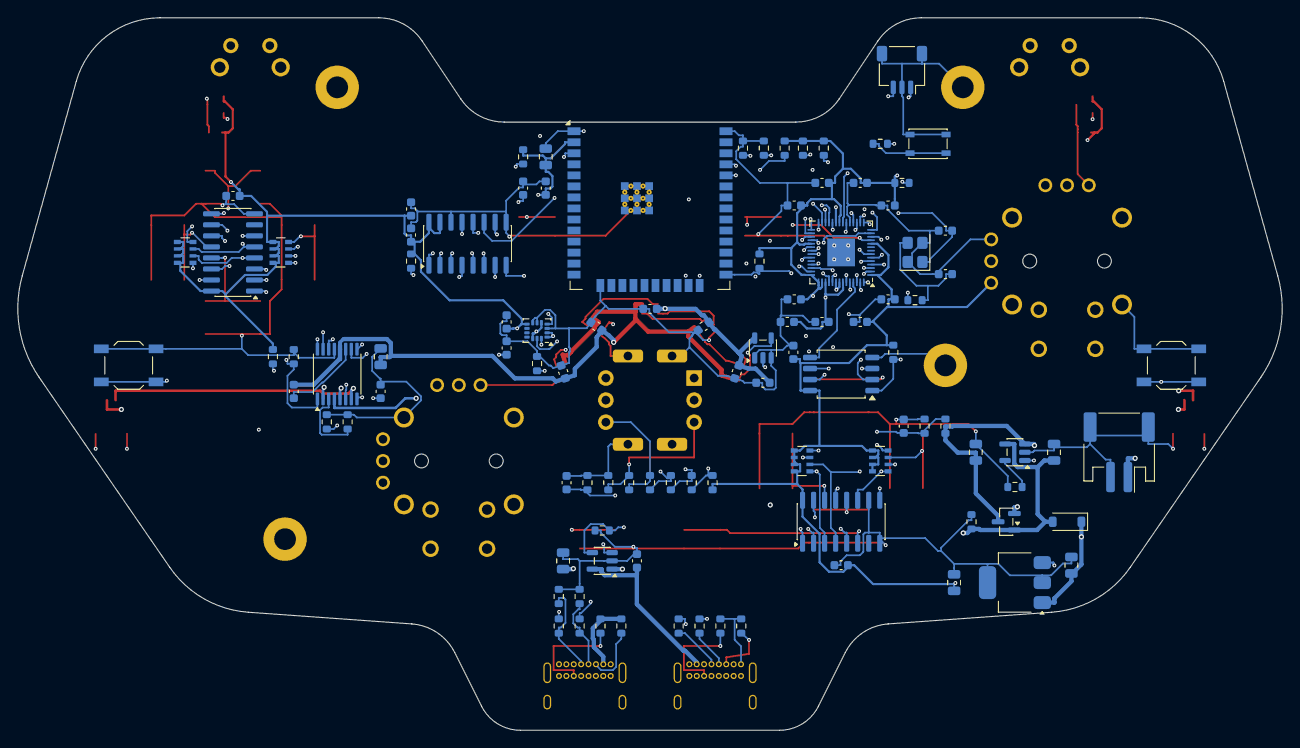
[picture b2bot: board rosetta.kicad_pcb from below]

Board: 6 copper layers, 145.5 x 82.0 mm, 135 parts (101 on the bottom side), 102 nets.
